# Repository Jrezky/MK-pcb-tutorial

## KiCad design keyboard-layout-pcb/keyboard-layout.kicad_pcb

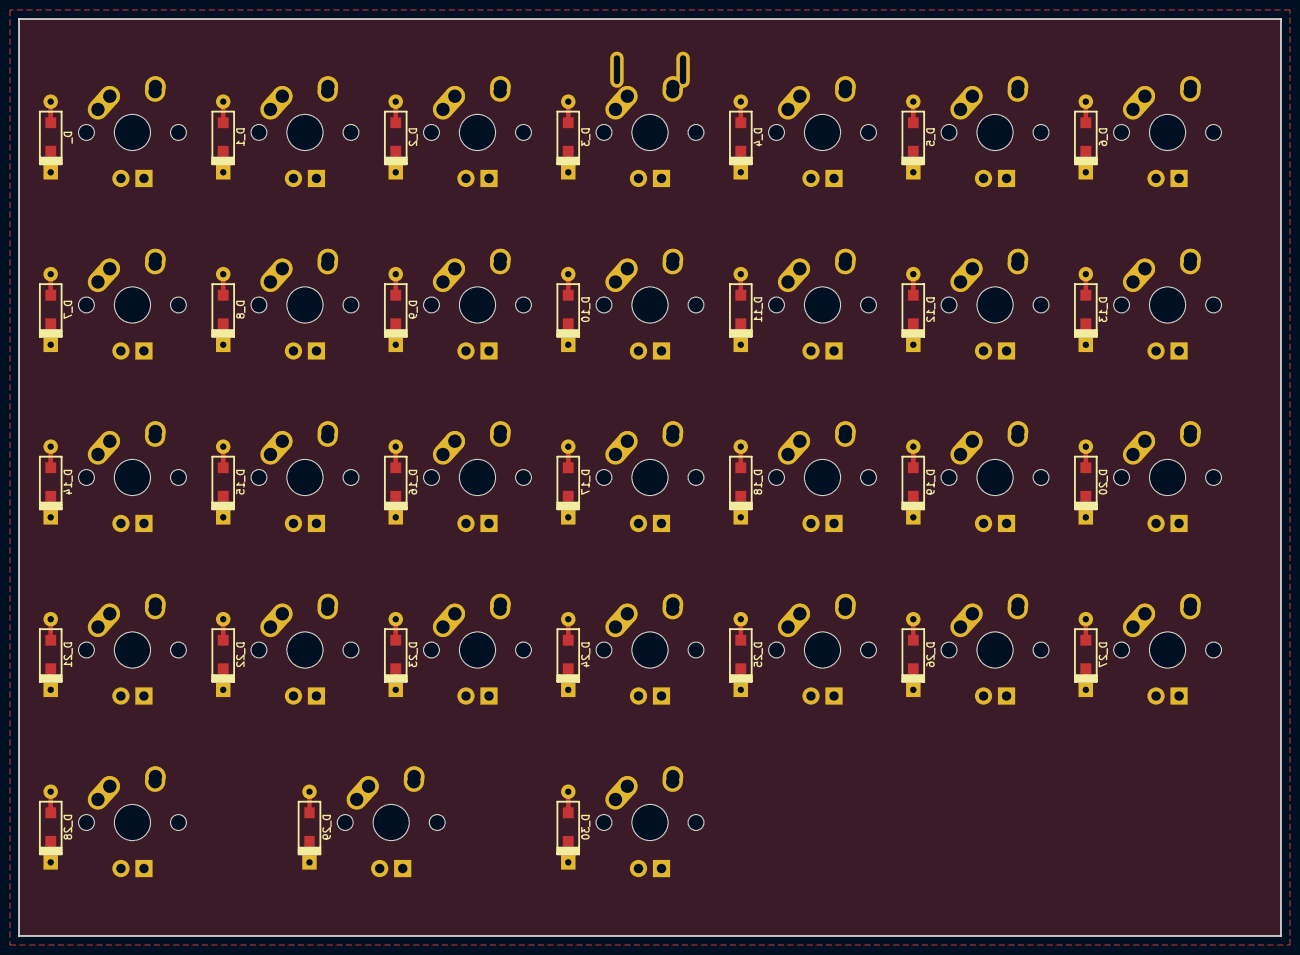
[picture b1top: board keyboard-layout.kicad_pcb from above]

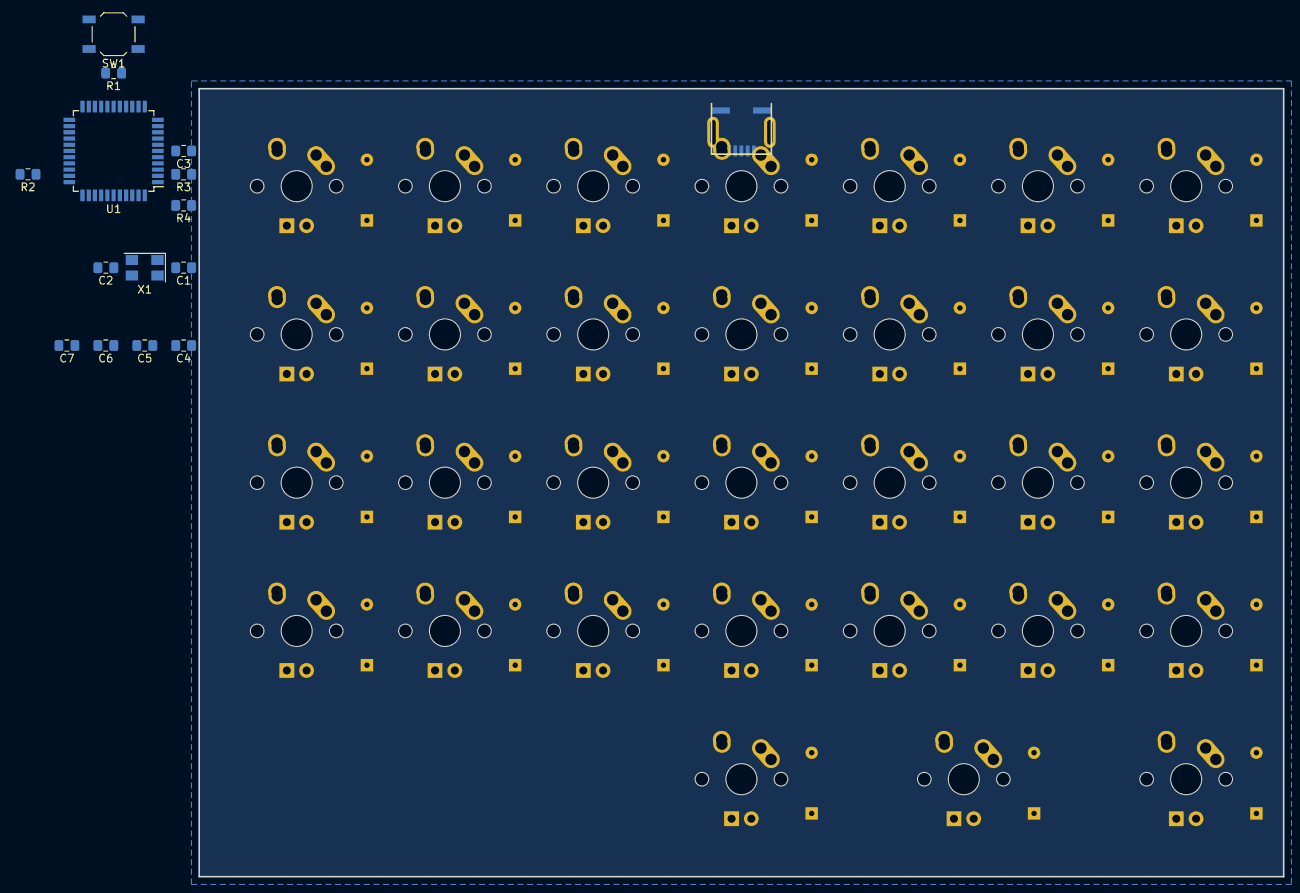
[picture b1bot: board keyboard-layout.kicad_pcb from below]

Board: 2 copper layers, 139.3 x 101.2 mm, 77 parts (15 on the bottom side), 49 nets, no tracks yet.

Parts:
C1, C2, C3, C4, C5, C6, C7: 22pF; C_0805_2012Metric_Pad1.15x1.40mm_HandSolder
D_, D_1, D_2, D_3, D_4, D_5, D_6, D_7, D_8, D_9, D_10, D_11, D_12, D_13, D_14, D_15, D_16, D_17, D_18, D_19, D_20, D_21, D_22, D_23, D_24, D_25, D_26, D_27, D_28, D_29, D_30: D; D_SOD123_axial
K_, K_1, K_2, K_3, K_4, K_5, K_6, K_7, K_8, K_9, K_10, K_11, K_12, K_13, K_14, K_15, K_16, K_17, K_18, K_19, K_20, K_21, K_22, K_23, K_24, K_25, K_26, K_27, K_28, K_29, K_30: KEYSW; MX-1U-NoLED
R1, R2: 10k; R_0805_2012Metric_Pad1.15x1.40mm_HandSolder
R3, R4: 22u; R_0805_2012Metric_Pad1.15x1.40mm_HandSolder
SW1: SW_PUSH; SW_SPST_TL3342
U1: ATMEGA32U4; TQFP-44_10x10mm_P0.8mm
USB1: USB_mini_micro_B; USB_miniB_hirose_5S8
X1: XTAL_GND; Crystal_SMD_5032-4Pin_5.0x3.2mm

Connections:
/col0: D_.1, D_7.1, D_14.1, D_21.1, D_28.1, U1.32
/col1: D_1.1, D_8.1, D_15.1, D_22.1, D_29.1, U1.31
/col2: D_2.1, D_9.1, D_16.1, D_23.1, D_30.1, U1.12
/col3: D_3.1, D_10.1, D_17.1, D_24.1, U1.30
/col4: D_4.1, D_11.1, D_18.1, D_25.1, U1.29
/col5: D_5.1, D_12.1, D_19.1, D_26.1, U1.28
/col6: D_6.1, D_13.1, D_20.1, D_27.1
GND: C1.2, C2.2, C3.2, C4.2, C5.2, C6.2, C7.2, R2.2, SW1.1, U1.5, U1.15, U1.23, USB1.5, USB1.6, X1.3
unnamed: C1.1, U1.16
unnamed: C2.1, U1.17
unnamed: C3.1, U1.6
unnamed: D_1.2, K_1.2
unnamed: D_2.2, K_2.2
unnamed: D_3.2, K_3.2
unnamed: D_4.2, K_4.2
unnamed: D_5.2, K_5.2
unnamed: D_6.2, K_6.2
unnamed: D_7.2, K_7.2
unnamed: D_8.2, K_8.2
unnamed: D_9.2, K_9.2
unnamed: D_10.2, K_10.2
unnamed: D_11.2, K_11.2
unnamed: D_12.2, K_12.2
unnamed: D_13.2, K_13.2
unnamed: D_14.2, K_14.2
unnamed: D_15.2, K_15.2
unnamed: D_16.2, K_16.2
unnamed: D_17.2, K_17.2
unnamed: D_18.2, K_18.2
unnamed: D_19.2, K_19.2
unnamed: D_20.2, K_20.2
unnamed: D_21.2, K_21.2
unnamed: D_22.2, K_22.2
unnamed: D_23.2, K_23.2
unnamed: D_24.2, K_24.2
unnamed: D_25.2, K_25.2
unnamed: D_26.2, K_26.2
unnamed: D_27.2, K_27.2
unnamed: D_28.2, K_28.2
unnamed: D_29.2, K_29.2
unnamed: D_30.2, K_30.2
unnamed: D_.2, K_.2
unnamed: R1.1, SW1.2, U1.13
unnamed: R2.1, U1.33
unnamed: R3.1, U1.3
unnamed: R4.1, U1.4
unnamed: R3.2, USB1.2
unnamed: R4.2, USB1.3
VCC: C4.1, C5.1, C6.1, C7.1, R1.2, U1.2, U1.14, U1.24, USB1.1

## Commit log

2019-08-26 initialize project
2019-08-26 adding libraries
2019-08-26 add footprint ibraries
2019-08-26 pre-physical-pcb
2019-08-26 pcb-tut-1
